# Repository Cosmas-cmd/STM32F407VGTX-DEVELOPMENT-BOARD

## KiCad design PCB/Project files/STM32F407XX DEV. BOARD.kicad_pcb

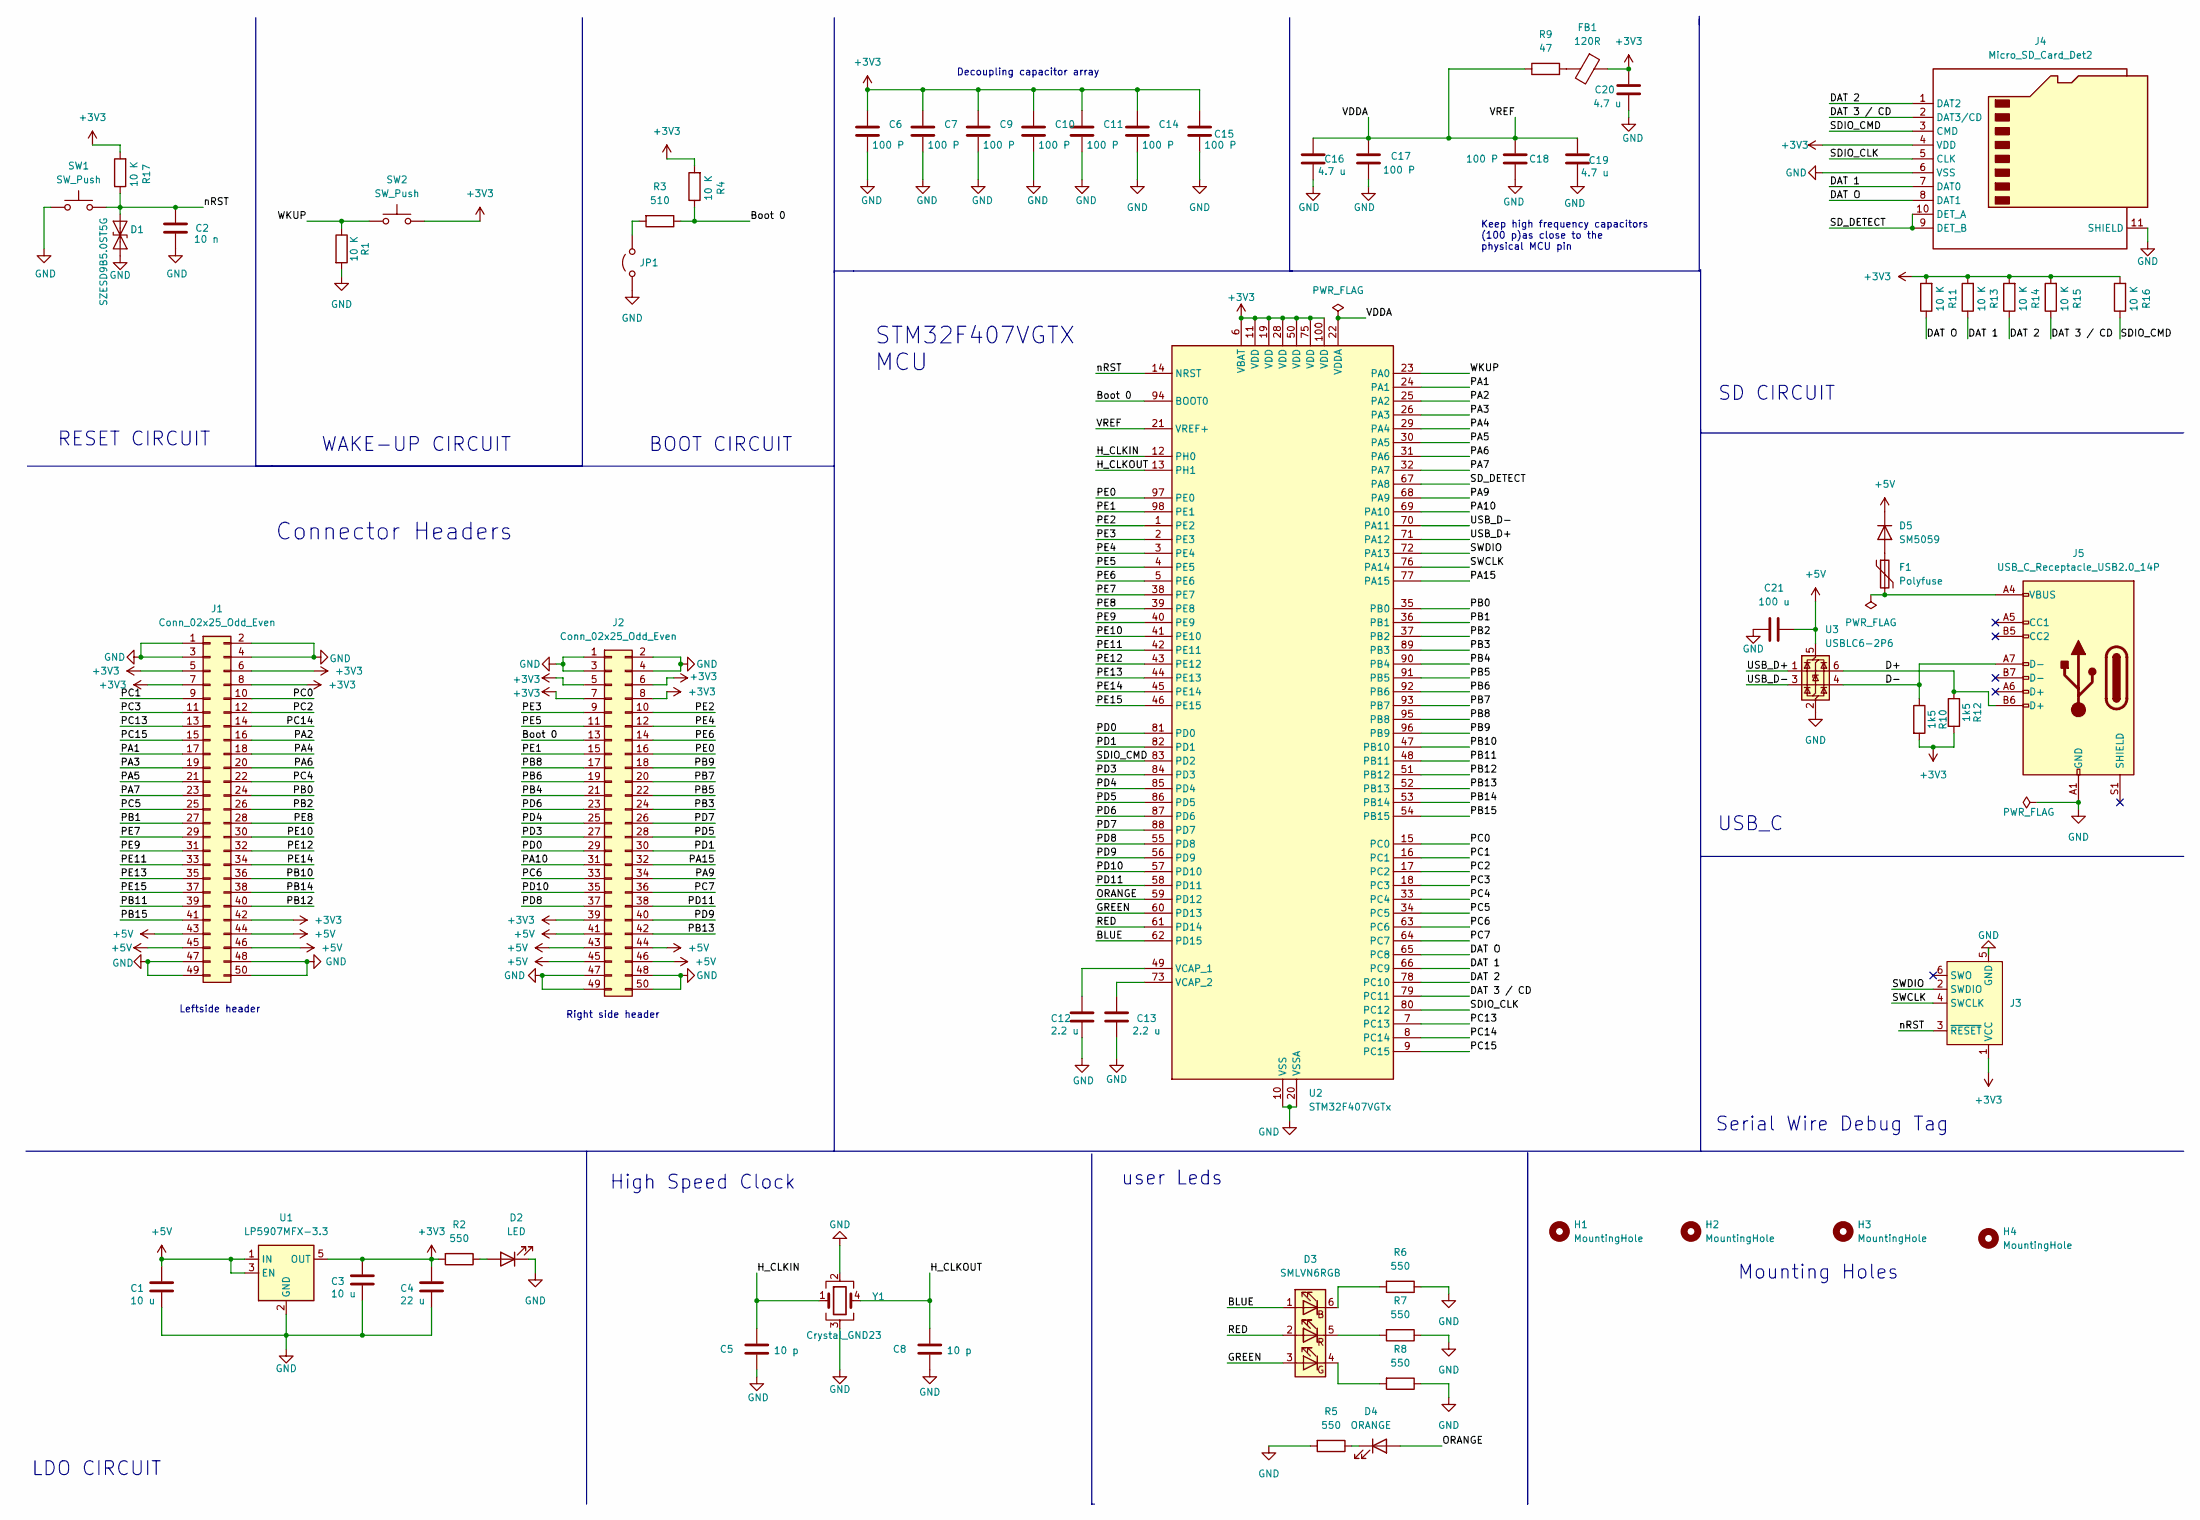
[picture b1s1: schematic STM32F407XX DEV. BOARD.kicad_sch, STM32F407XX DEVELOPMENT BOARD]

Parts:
C1, C3: 10 u; C_0402_1005Metric
C2: 10 n; C_0402_1005Metric
C4: 22 u; C_0402_1005Metric
C5, C8: 10 p; C_0603_1608Metric
C6, C7, C9, C10, C11, C14, C15, C17, C18: 100 P; C_0402_1005Metric
C12, C13: 2.2 u; C_0402_1005Metric
C16, C19, C20: 4.7 u; C_0402_1005Metric
C21: 100 u; C_0603_1608Metric
D1: SZESD9B5.0ST5G; D_SOD-923
D2: LED; LED_0805_2012Metric
D3: SMLVN6RGB; LED_RGB_5050-6
D4: ORANGE; LED_0805_2012Metric
D5: SM5059; D_SMA
F1: Polyfuse; Fuse_1206_3216Metric_Pad1.42x1.75mm_HandSolder
FB1: 120R; L_0603_1608Metric
H1, H2, H3, H4: MountingHole; MountingHole_2.5mm
J1, J2: Conn_02x25_Odd_Even; PinHeader_2x25_P2.54mm_Vertical
J3: Conn_ARM_SWD_TagConnect_TC2030-NL; Tag-Connect_TC2030-IDC-NL_2x03_P1.27mm_Vertical
J4: Micro_SD_Card_Det2; microSD_HC_Hirose_DM3AT-SF-PEJM5
J5: USB_C_Receptacle_USB2.0_14P; USB_C_Receptacle_GCT_USB4105-xx-A_16P_TopMnt_Horizontal
JP1: Jumper_2_Open; SolderJumper-2_P1.3mm_Open_TrianglePad1.0x1.5mm
R1, R4, R11, R13, R14, R15, R16, R17: 10 K; R_0603_1608Metric
R2, R5, R6, R7, R8: 550; R_0603_1608Metric
R3: 510; R_0603_1608Metric
R9: 47; R_0603_1608Metric
R10, R12: 1k5; R_0603_1608Metric
SW1, SW2: SW_Push; SW_PUSH_6mm
U1: LP5907MFX-3.3; SOT-23-5
U2: STM32F407VGTx; LQFP-100_14x14mm_P0.5mm
U3: USBLC6-2P6; SOT-666
Y1: Crystal_GND23; Crystal_SMD_3225-4Pin_3.2x2.5mm

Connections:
+3V3: C3.1, C4.1, C6.1, C7.1, C9.1, C10.1, C11.1, C14.1, C15.1, C20.1, FB1.1, J1.5, J1.6, J1.7, J1.8, J1.42, J2.5, J2.6, J2.7, J2.8, J2.39, J3.1 (VCC), J4.4 (VDD), R2.2, R4.2, R10.2, R11.2, R12.2, R13.2, R14.2, R15.2, R16.2, R17.2, SW2.2, U1.5 (OUT), U2.6 (VBAT), U2.11 (VDD), U2.19 (VDD), U2.28 (VDD), U2.50 (VDD), U2.75 (VDD), U2.100 (VDD)
+5V: C1.1, C21.2, D5.1 (K), J1.43, J1.44, J1.45, J1.46, J2.41, J2.43, J2.44, J2.45, J2.46, U1.1 (IN), U1.3 (EN), U3.5 (VBUS)
/BLUE: D3.1 (BA), U2.62 (PD15); also elsewhere on the board
/Boot 0: J2.13, R3.1, R4.1, U2.94 (BOOT0)
/D+: J5.B6 (D+), R12.1, U3.6 (I/O1)
/D-: J5.A7 (D-), R10.1, U3.4 (I/O2)
/DAT 1: J4.7 (DAT0), R13.1, U2.66 (PC9)
/DAT 2: J4.1 (DAT2), R14.1, U2.78 (PC10)
/DAT 3 / CD: J4.2 (DAT3/CD), R15.1, U2.79 (PC11)
/DAT O: J4.8 (DAT1), R11.1, U2.65 (PC8)
/GREEN: D3.3 (GA), U2.60 (PD13); also elsewhere on the board
/H_CLKIN: C5.1, U2.12 (PH0), Y1.1
/H_CLKOUT: C8.1, U2.13 (PH1), Y1.4
/ORANGE: D4.2 (A), U2.59 (PD12)
/PA1: J1.17, U2.24 (PA1)
/PA2: J1.16, U2.25 (PA2)
/PA3: J1.19, U2.26 (PA3)
/PA4: J1.18, U2.29 (PA4)
/PA5: J1.21, U2.30 (PA5)
/PA6: J1.20, U2.31 (PA6)
/PA7: J1.23, U2.32 (PA7)
/PA9: J2.34, U2.68 (PA9)
/PA10: J2.31, U2.69 (PA10)
/PA15: J2.32, U2.77 (PA15)
/PB0: J1.24, U2.35 (PB0)
/PB1: J1.27, U2.36 (PB1)
/PB2: J1.26, U2.37 (PB2)
/PB3: J2.24, U2.89 (PB3)
/PB4: J2.21, U2.90 (PB4)
/PB5: J2.22, U2.91 (PB5)
/PB6: J2.19, U2.92 (PB6)
/PB7: J2.20, U2.93 (PB7)
/PB8: J2.17, U2.95 (PB8)
/PB9: J2.18, U2.96 (PB9)
/PB10: J1.36, U2.47 (PB10)
/PB11: J1.39, U2.48 (PB11)
/PB12: J1.40, U2.51 (PB12)
/PB13: J2.42, U2.52 (PB13)
/PB14: J1.38, U2.53 (PB14)
/PB15: J1.41, U2.54 (PB15)
/PC0: J1.10, U2.15 (PC0)
/PC1: J1.9, U2.16 (PC1)
/PC2: J1.12, U2.17 (PC2)
/PC3: J1.11, U2.18 (PC3)
/PC4: J1.22, U2.33 (PC4)
/PC5: J1.25, U2.34 (PC5)
/PC6: J2.33, U2.63 (PC6)
/PC7: J2.36, U2.64 (PC7)
/PC13: J1.13, U2.7 (PC13)
/PC14: J1.14, U2.8 (PC14)
/PC15: J1.15, U2.9 (PC15)
/PD0: J2.29, U2.81 (PD0)
/PD1: J2.30, U2.82 (PD1)
/PD3: J2.27, U2.84 (PD3)
/PD4: J2.25, U2.85 (PD4)
/PD5: J2.28, U2.86 (PD5)
/PD6: J2.23, U2.87 (PD6)
/PD7: J2.26, U2.88 (PD7)
/PD8: J2.37, U2.55 (PD8)
/PD9: J2.40, U2.56 (PD9)
/PD10: J2.35, U2.57 (PD10)
/PD11: J2.38, U2.58 (PD11)
/PE0: J2.16, U2.97 (PE0)
/PE1: J2.15, U2.98 (PE1)
/PE2: J2.10, U2.1 (PE2)
/PE3: J2.9, U2.2 (PE3)
/PE4: J2.12, U2.3 (PE4)
/PE5: J2.11, U2.4 (PE5)
/PE6: J2.14, U2.5 (PE6)
/PE7: J1.29, U2.38 (PE7)
/PE8: J1.28, U2.39 (PE8)
/PE9: J1.31, U2.40 (PE9)
/PE10: J1.30, U2.41 (PE10)
/PE11: J1.33, U2.42 (PE11)
/PE12: J1.32, U2.43 (PE12)
/PE13: J1.35, U2.44 (PE13)
/PE14: J1.34, U2.45 (PE14)
/PE15: J1.37, U2.46 (PE15)
/RED: D3.2 (RA), U2.61 (PD14); also elsewhere on the board
/SDIO_CLK: J4.5 (CLK), U2.80 (PC12)
/SDIO_CMD: J4.3 (CMD), R16.1, U2.83 (PD2)
/SD_DETECT: J4.9 (DET_B), J4.10 (DET_A), U2.67 (PA8)
/SWCLK: J3.4 (SWCLK), U2.76 (PA14)
/SWDIO: J3.2 (SWDIO), U2.72 (PA13)
/USB_D+: U2.71 (PA12), U3.1 (I/O1)
/USB_D-: U2.70 (PA11), U3.3 (I/O2)
/VDDA: C16.1, C17.1, C18.1, C19.1, R9.1, U2.21 (VREF+), U2.22 (VDDA)
/WKUP: R1.1, SW2.1, U2.23 (PA0)
/nRST: C2.1, D1.2 (A2), J3.3 (~RESET), R17.1, SW1.2, U2.14 (NRST)
GND: C1.2, C2.2, C3.2, C4.2, C5.2, C6.2, C7.2, C8.2, C9.2, C10.2, C11.2, C12.2, C13.2, C14.2, C15.2, C16.2, C17.2, C18.2, C19.2, C20.2, C21.1, D1.1 (A1), D2.1 (K), J1.1, J1.2, J1.3, J1.4, J1.47, J1.48, J1.49, J1.50, J2.1, J2.2, J2.3, J2.4, J2.47, J2.48, J2.49, J2.50, J3.5 (GND), J4.6 (VSS), J4.11 (SHIELD), J5.A1 (GND), J5.A12 (GND), J5.B1 (GND), J5.B12 (GND), JP1.1 (A), R1.2, R5.2, R6.1, R7.1, R8.1, SW1.1, U1.2 (GND), U2.10 (VSS), U2.20 (VSSA), U2.27 (VSS), U2.74 (VSS), U2.99 (VSS), U3.2 (GND), Y1.2, Y1.3
unnamed: D2.2 (A), R2.1
unnamed 91: D3.6 (BK), R6.2; also elsewhere on the board
unnamed 92: D3.4 (GK), R8.2; also elsewhere on the board
unnamed 93: D3.5 (RK), R7.2; also elsewhere on the board
unnamed: D4.1 (K), R5.1
unnamed: D5.2 (A), F1.1
unnamed: F1.2, J5.A4 (VBUS), J5.A9 (VBUS), J5.B4 (VBUS), J5.B9 (VBUS)
unnamed: FB1.2, R9.2
unnamed: JP1.2 (B), R3.2
unnamed: C12.1, U2.49 (VCAP_1)
unnamed: C13.1, U2.73 (VCAP_2)

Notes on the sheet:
High Speed Clock
USB_C
BOOT CIRCUIT
Leftside header
Mounting Holes
Decoupling capacitor array
Serial Wire Debug Tag
SD CIRCUIT
LDO CIRCUIT
WAKE-UP CIRCUIT
Keep high frequency capacitors (100 p)as close to the physical MCU pin
RESET CIRCUIT
Right side header
user Leds
STM32F407VGTX MCU
Connector Headers

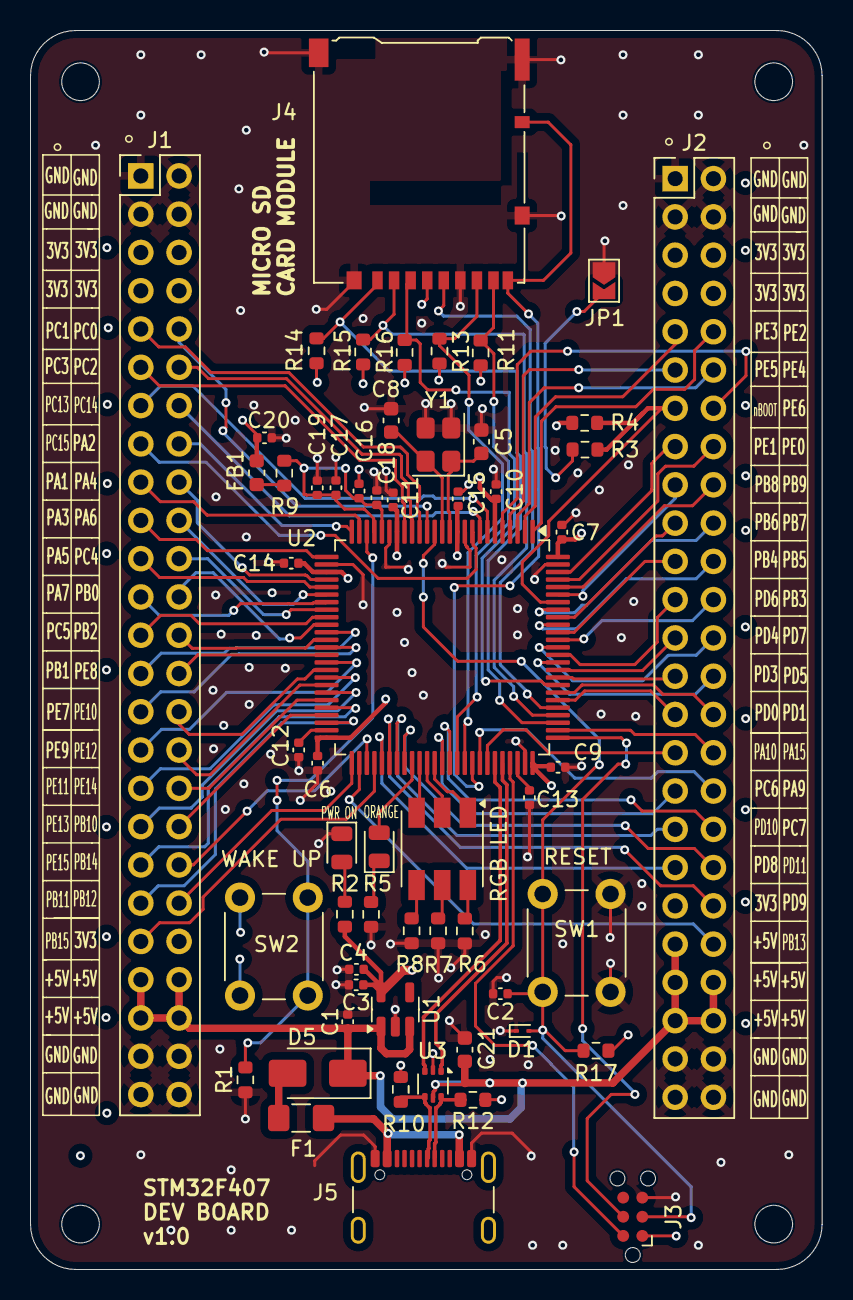
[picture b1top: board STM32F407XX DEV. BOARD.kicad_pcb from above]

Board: 4 copper layers, 52.5 x 82.2 mm, 61 parts (0 on the bottom side), 101 nets.

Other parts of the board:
RGB LED: SMLVN6RGB; LED_RGB_5050-6

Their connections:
/BLUE: RGB LED.1 (BA); also elsewhere on the board
/GREEN: RGB LED.3 (GA); also elsewhere on the board
/RED: RGB LED.2 (RA); also elsewhere on the board
unnamed 91: RGB LED.6 (BK); also elsewhere on the board
unnamed 92: RGB LED.4 (GK); also elsewhere on the board
unnamed 93: RGB LED.5 (RK); also elsewhere on the board
